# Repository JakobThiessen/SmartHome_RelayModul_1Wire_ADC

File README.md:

# SmartHome_RelayModul_1Wire_ADC

beachte Änderungen in [Hardwarebeschreibung](hardware/readme.md)

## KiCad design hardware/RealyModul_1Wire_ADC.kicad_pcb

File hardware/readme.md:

# Schaltplan

# Layout

# Bauteile

# Verdrahtungsplan

# Änderungen

Folgende Änderung muss vorgenommen werden:

IO12 kein PullUp (probleme beim booten)

IO34, IO35, IO36 and IO39 --> input only

IO34 --> IO13\
IO35 --> IO25

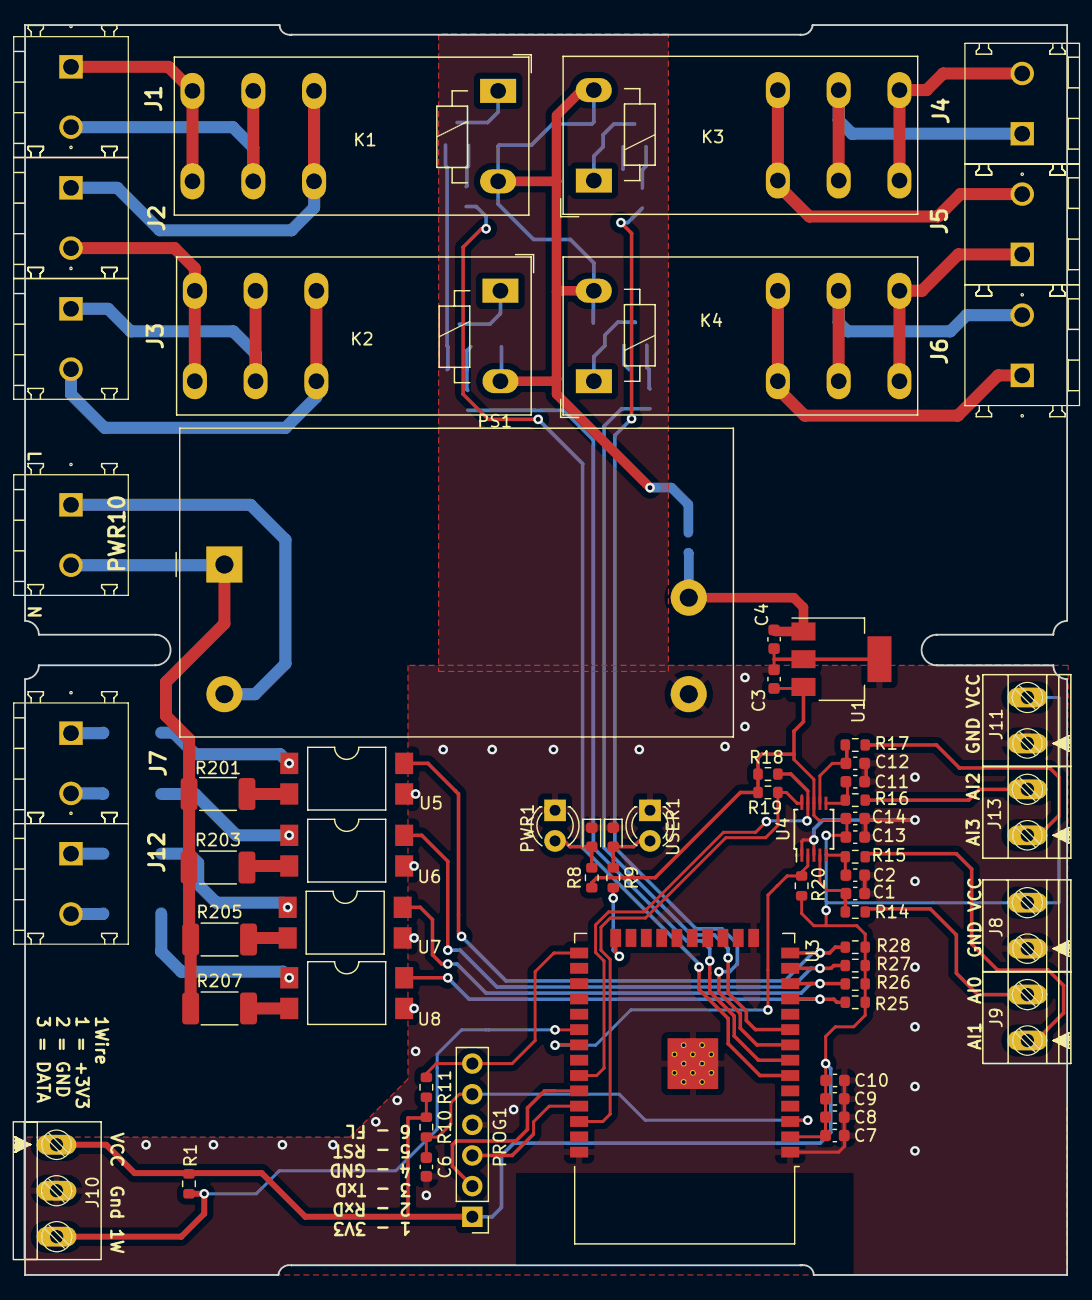
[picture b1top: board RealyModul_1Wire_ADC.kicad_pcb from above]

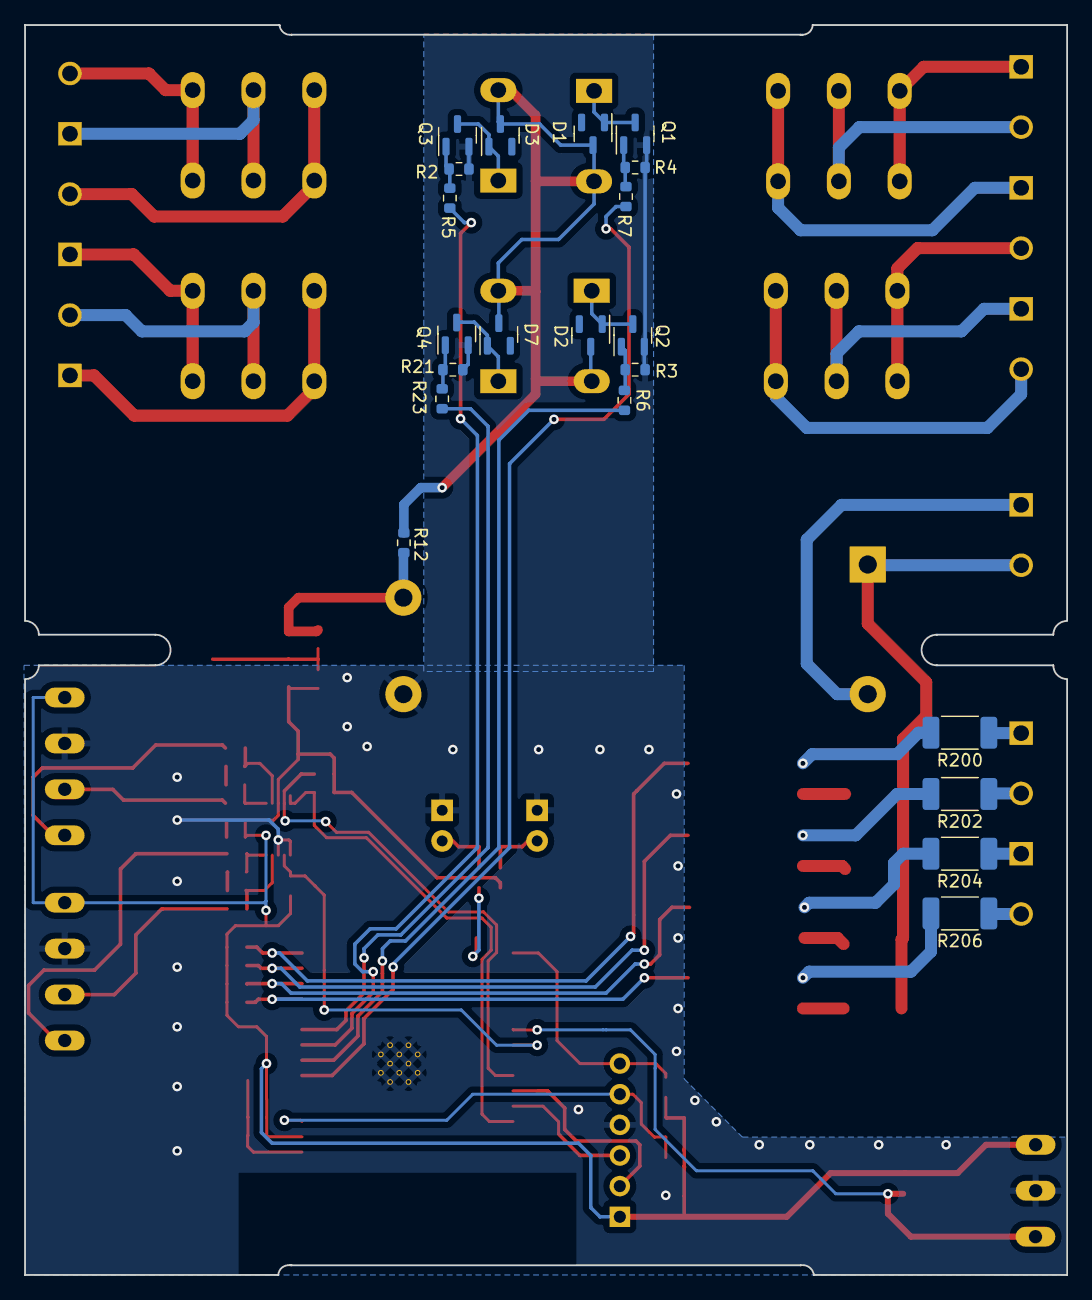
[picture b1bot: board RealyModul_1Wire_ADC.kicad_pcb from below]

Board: 2 copper layers, 86.4 x 103.6 mm, 85 parts (21 on the bottom side), 65 nets.

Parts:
C1, C2, C6, C7, C8, C11, C12, C13: 100nF; C_0603_1608Metric
C3: 4,7µF/6,3V; C_0603_1608Metric
C4: 10µF/6,3V; C_0603_1608Metric
C9, C10, C14: 1µF; C_0603_1608Metric
D1, D2, D3, D7: BAS21; SOT-23
D4, D5: LED; LED_D3.0mm_Clear
J1, J2, J3, J4, J5, J6, J7, J12: Conn_01x03; MKDSN 2,5-2-5.08
J8, J9, J11, J13: Conn_01x02; MKDS_1_2_3.81
J10: Conn_01x03; MKDS_1_3_3.81
K1, K2, K3, K4: RT314A12; Relay_SPDT_Schrack-RT1-16A-FormC_RM5mm
PROG1: Conn_01x06; PinHeader_1x06_P2.54mm_Vertical
PS1: IRM-05-5; Converter_ACDC_MeanWell_IRM-05-xx_THT
PWR1: green; LED_0603_1608Metric
PWR10: Conn_01x03; MKDSN 2,5-2-5.08
Q1, Q2, Q3, Q4: BSS123; SOT-23
R1: 4k7; R_0603_1608Metric
R2, R3, R4, R21: 100k; R_0603_1608Metric
R5, R6, R7, R14, R15, R16, R17, R23: 100; R_0603_1608Metric
R8, R9: 470R; R_0603_1608Metric
R10, R11, R18, R19, R20, R25, R26, R27, R28: 10k; R_0603_1608Metric
R12: 0R0; R_0603_1608Metric
R200, R201, R202, R203, R204, R205, R206, R207: R; R_2010_5025Metric_Pad1.40x2.65mm_HandSolder
U1: LT1129-3.3_SOT223; SOT-223-3_TabPin2
U3: ESP32-WROOM-32D; ESP32-WROOM-32
U4: ADS1115IDGS; TSSOP-10_3x3mm_P0.5mm
U5, U6, U7, U8: SFH6206-1T; SMDIP-4_W9.53mm_Clearance8mm
USER1: blue; LED_0603_1608Metric

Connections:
+3.3V: C3.1, C7.1, C8.1, C9.1, C10.1, C13.1, C14.1, J8.2, J10.1, J11.2, PROG1.1, R1.1, R8.1, R10.1, R11.1, R18.1, R19.1, R20.1, R25.1, R26.1, R27.1, R28.1, U1.3 (VO), U3.2 (VDD), U4.8 (VDD)
+5V: C4.1, PS1.4 (+Vo), R12.1, U1.1 (VI)
/1Wire: J10.3, R1.2, U3.30 (IO18)
/ADC_ALERT: R20.2, U3.31 (IO19), U4.2 (ALERT/RDY)
/INPUT_01: R25.2, U3.11 (IO26), U8.4
/INPUT_02: R26.2, U3.12 (IO27), U7.4
/INPUT_03: R27.2, U3.13 (IO14), U6.4
/INPUT_04: R28.2, U3.14 (IO12), U5.4
/IO0: PROG1.6, R11.2, U3.25 (IO0)
/IO32_K4: R23.2, U3.9 (IO33)
/IO33_K3: R5.2, U3.8 (IO32)
/IO34_K1: R7.2, U3.6 (IO34)
/IO35_K2: R6.2, U3.7 (IO35)
/IO_02: R9.1, U3.24 (IO2)
/POWER_N: PS1.1 (AC/N), PWR10.2, R201.1, R203.1, R205.1, R207.1
/RST: C6.1, PROG1.5, R10.2, U3.3 (EN)
/RXD: PROG1.2, U3.34 (RXD0/IO3)
/SCL: R19.2, U3.36 (IO22), U4.10 (SCL)
/SDA: R18.2, U3.33 (IO21), U4.9 (SDA)
/TXD: PROG1.3, U3.35 (TXD0/IO1)
GND: C1.2, C2.2, C3.2, C4.2, C6.2, C7.2, C8.2, C9.2, C10.2, C11.2, C12.2, C13.2, C14.2, D4.1 (K), D5.1 (K), J8.1, J10.2, J11.1, PROG1.4, PS1.3 (-Vo), PWR1.1 (K), Q1.2 (S), Q2.2 (S), Q3.2 (S), Q4.2 (S), R2.2, R3.2, R4.2, R21.2, U1.2 (GND), U3.1 (GND), U3.15 (GND), U3.38 (GND), U3.39 (GND), U4.1 (ADDR), U4.3 (GND), U5.3, U6.3, U7.3, U8.3, USER1.1 (K)
unnamed: D1.1 (A), K1.A1, Q1.3 (D)
unnamed: D2.1 (A), K2.A1, Q2.3 (D)
unnamed: D3.1 (A), K3.A1, Q3.3 (D)
unnamed: D4.2 (A), PWR1.2 (A), R8.2
unnamed: D5.2 (A), R9.2, USER1.2 (A)
unnamed: D7.1 (A), K4.A1, Q4.3 (D)
unnamed: J1.1, K1.14
unnamed: J1.2, K1.11
unnamed: J2.1, K1.12
unnamed: J2.2, K2.14
unnamed: J3.1, K2.11
unnamed: J3.2, K2.12
unnamed: J4.1, K3.11
unnamed: J4.2, K3.14
unnamed: J5.1, K4.14
unnamed: J5.2, K3.12
unnamed: J6.1, K4.12
unnamed: J6.2, K4.11
unnamed: J7.1, R200.1
unnamed: J7.2, R202.1
unnamed: J9.1, R15.1
unnamed: J9.2, R14.1
unnamed: J12.1, R204.1
unnamed: J12.2, R206.1
unnamed: J13.1, R17.1
unnamed: J13.2, R16.1
unnamed: PS1.2 (AC/L), PWR10.1
unnamed: Q1.1 (G), R4.1, R7.1
unnamed: Q2.1 (G), R3.1, R6.1
unnamed: Q3.1 (G), R2.1, R5.1
unnamed: Q4.1 (G), R21.1, R23.1
unnamed: R200.2, U5.1
unnamed: R201.2, U5.2
unnamed: R202.2, U6.1
unnamed: R203.2, U6.2
unnamed: R204.2, U7.1
unnamed: R205.2, U7.2
unnamed: R206.2, U8.1
unnamed: R207.2, U8.2
unnamed: C1.1, R14.2, U4.4 (AIN0)
unnamed: C2.1, R15.2, U4.5 (AIN1)
unnamed: C11.1, R16.2, U4.6 (AIN2)
unnamed: C12.1, R17.2, U4.7 (AIN3)
Vdrive: D1.3 (K), D2.3 (K), D3.3 (K), D7.3 (K), K1.A2, K2.A2, K3.A2, K4.A2, R12.2

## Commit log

2023-07-08 initial
2023-07-08 Layout
2023-07-08 Schaltplan angepasst
2023-07-08 Bild aktualisiert
2023-07-20 änderung
2023-07-21 fast fertig
2023-07-24 fertig
2023-07-30 create gerber file
2023-07-30 rename files: from "RealyModul_1Wire_ADC" to "RelayModul_1Wire_ADC"
2023-07-30 add files
2023-08-17 bild hinzugefügt
